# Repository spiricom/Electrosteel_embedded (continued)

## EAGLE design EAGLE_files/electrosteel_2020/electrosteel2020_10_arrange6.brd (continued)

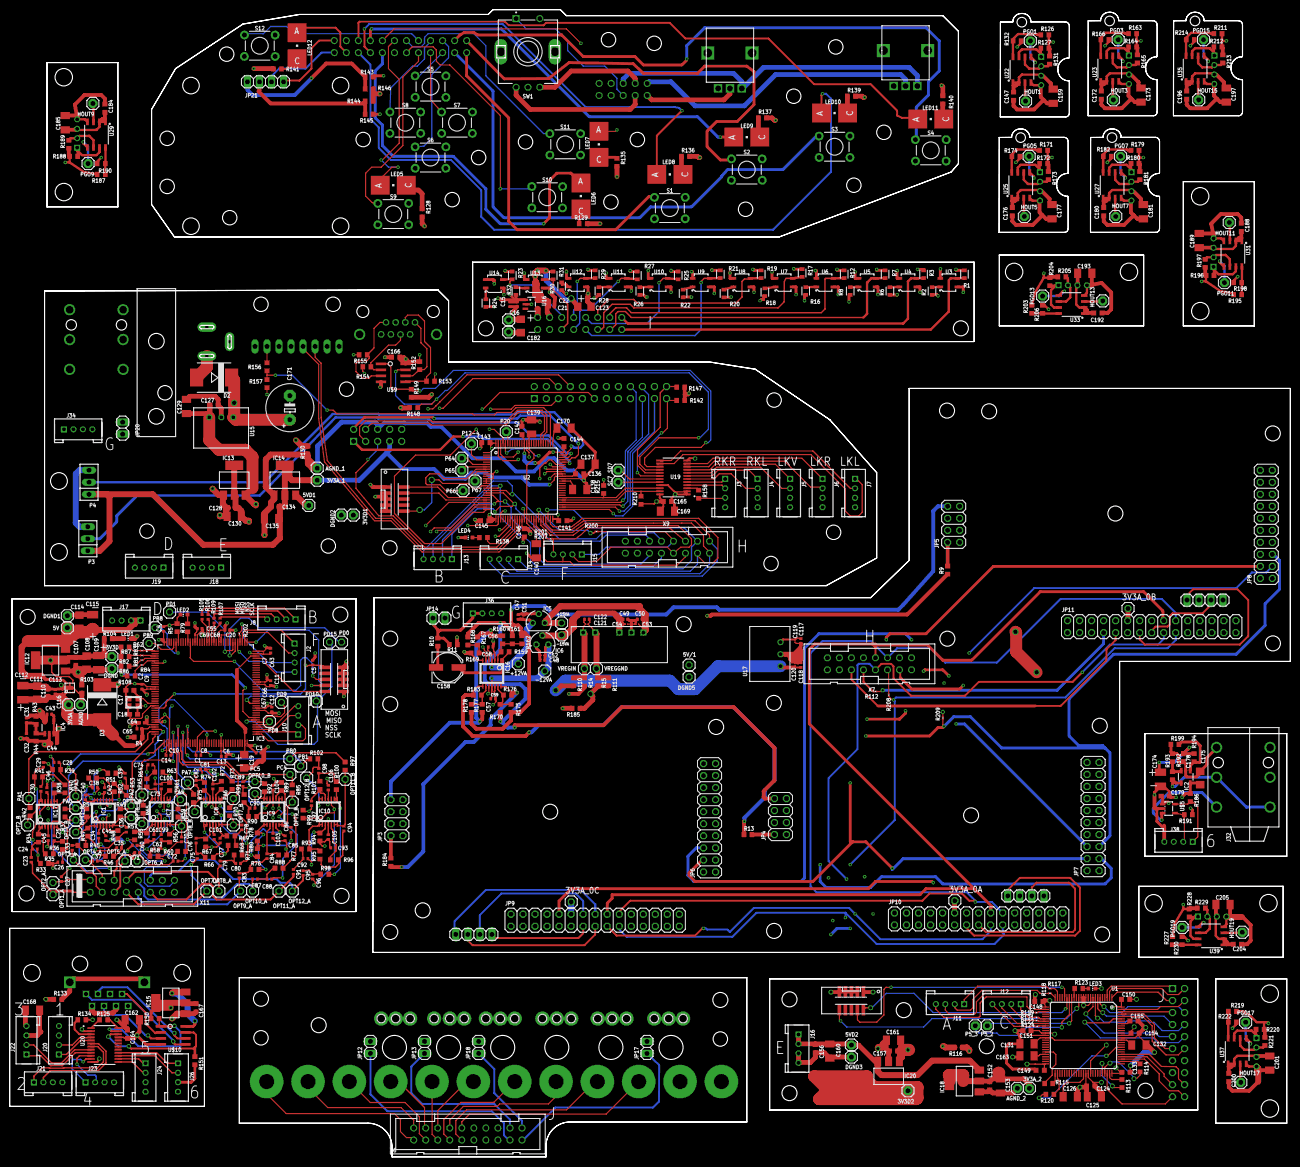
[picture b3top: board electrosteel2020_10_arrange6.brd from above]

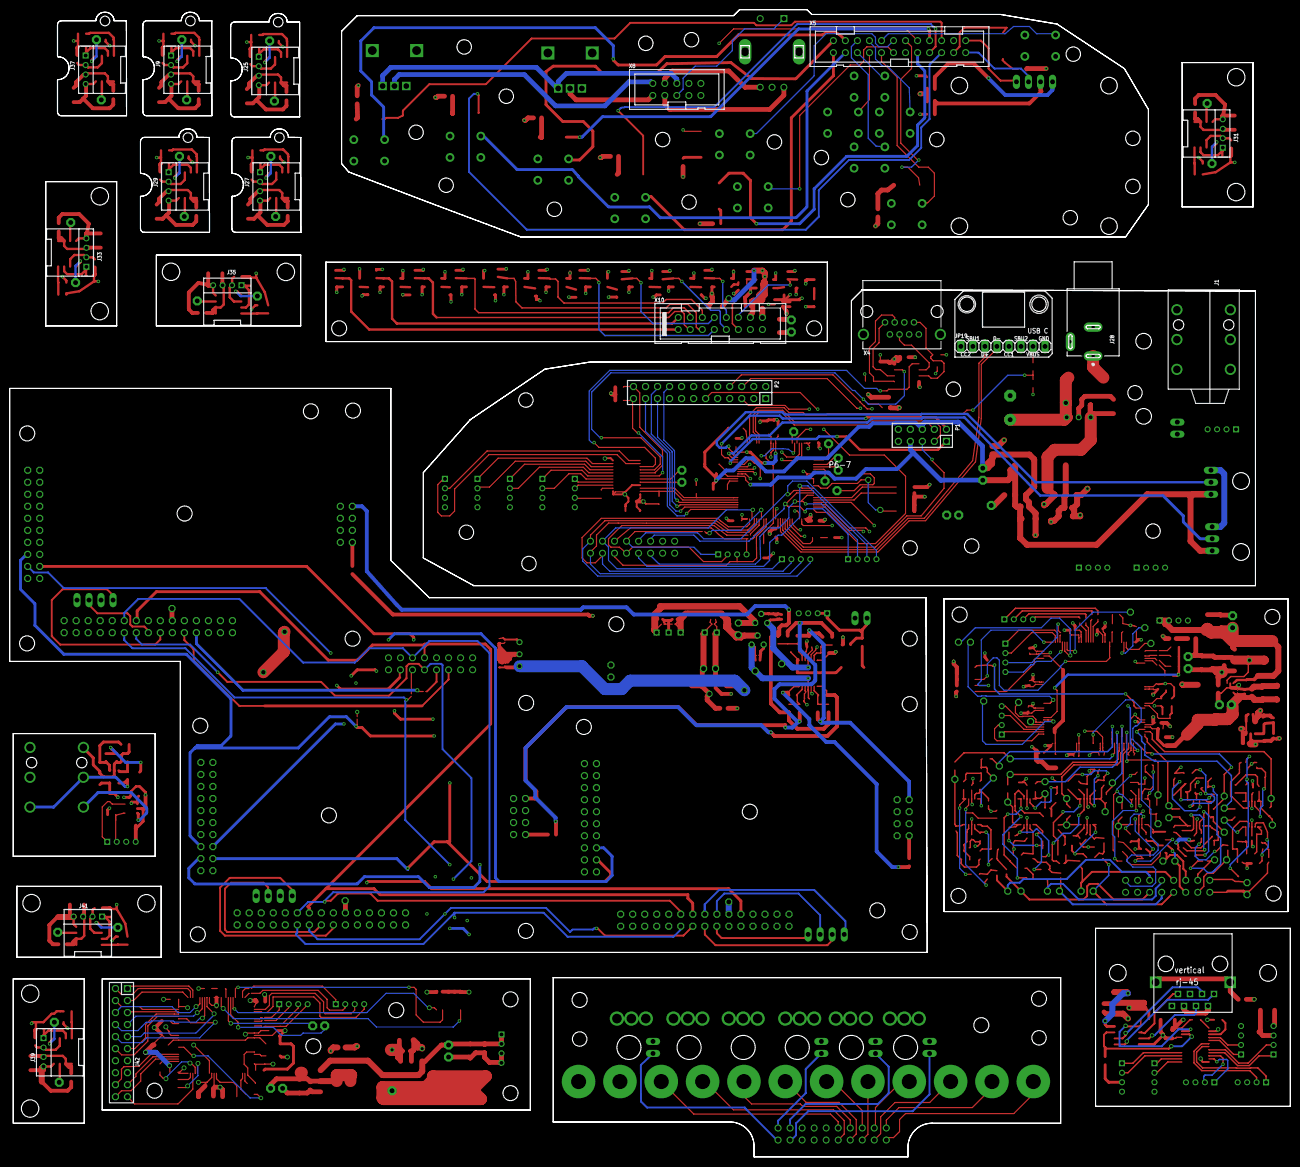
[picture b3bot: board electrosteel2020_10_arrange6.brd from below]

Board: 4 copper layers, 270.5 x 242.3 mm, 678 parts (21 on the bottom side), 529 nets.

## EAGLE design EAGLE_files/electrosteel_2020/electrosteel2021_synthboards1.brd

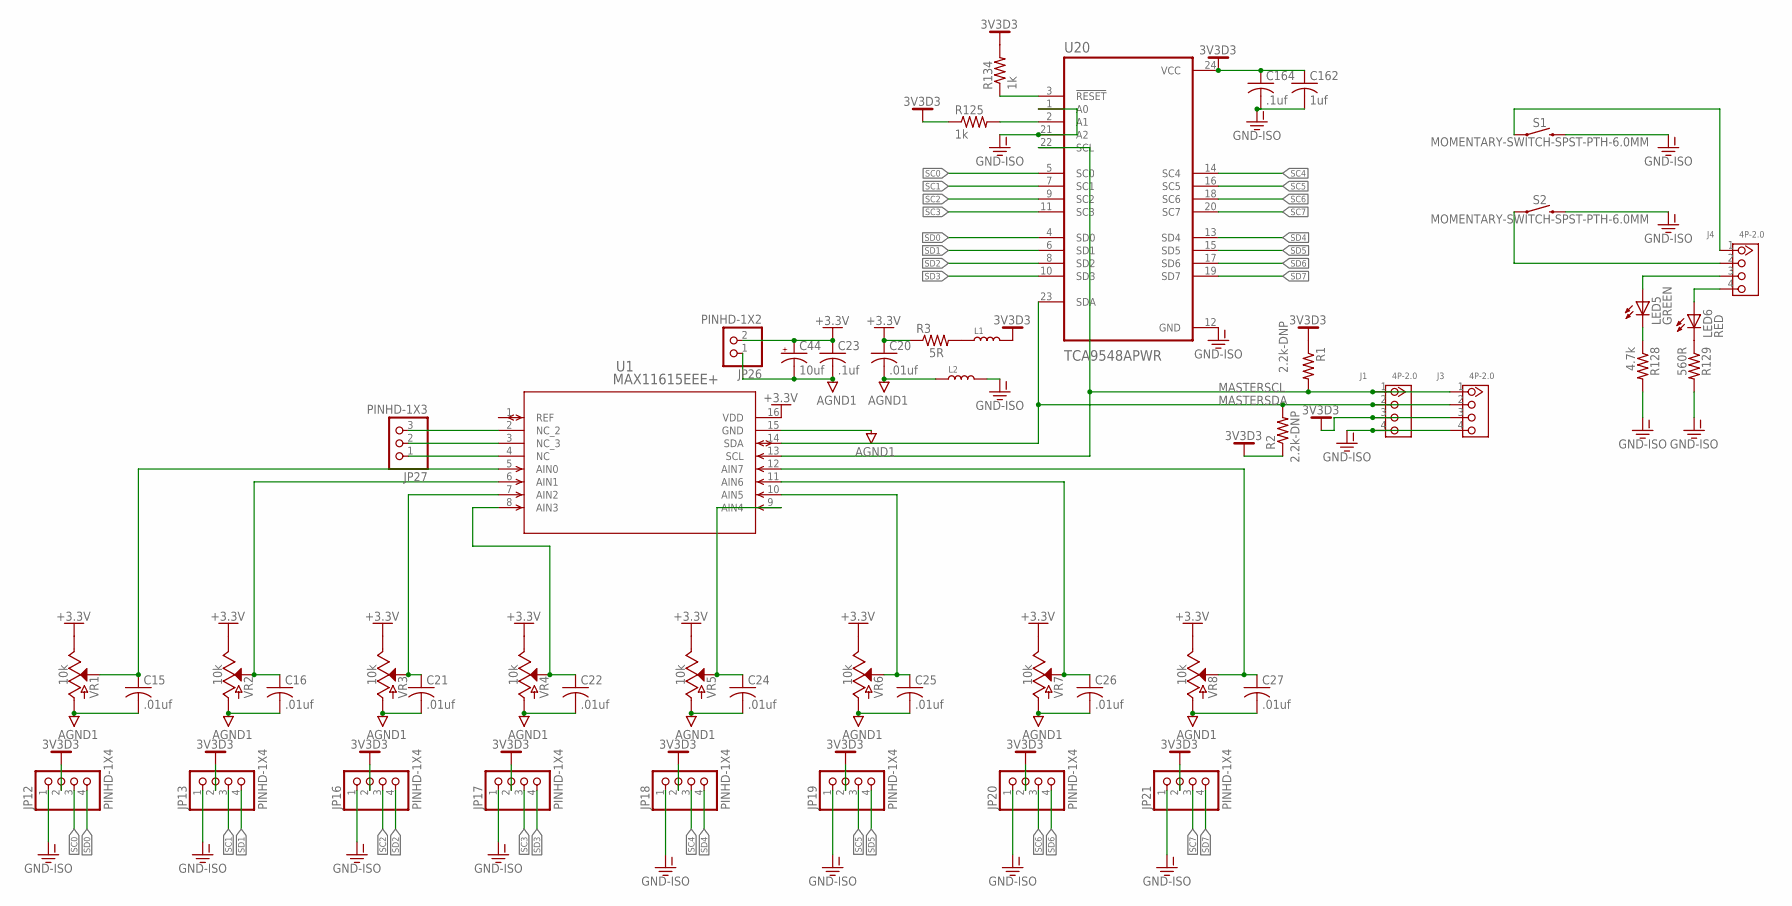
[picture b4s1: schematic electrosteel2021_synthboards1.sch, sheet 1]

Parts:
C15, C16, C20, C21, C22, C24, C25, C26, C27: .01uf; C0603; PARTNO CC0603KRX7R8BB103
C23, C164: .1uf; C0603; PARTNO CC0603KRX7R8BB104
C44: 10uf; SMC_B; PARTNO TAJB106K025RNJ
C162: 1uf; C1206K; PARTNO C3216X7R1E105K085AA
J1, J3, J4: 4P-2.0; HW4-2.0; PARTNO *DNP
JP12, JP13, JP16, JP17, JP18, JP19, JP20, JP21: PINHD-1X4; 1X04; PARTNO *DNP
JP26: PINHD-1X2; 1X02; PARTNO *DNP
JP27: PINHD-1X3; 1X03; PARTNO *DNP
L1, L2: INDUCTOR/FERRITE-BEAD0603; INDUCTOR_L0603; PARTNO FBMH1608HM470-TV
LED5: GREEN; P-LCC-2; PARTNO HSMM-A101-R00J1
LED6: RED; P-LCC-2; PARTNO HSMZ-A100-R00J1
R1, R2: 2.2k-DNP; R0603; PARTNO *DNP
R3: 5R; R0603; PARTNO RC0603JR-075R1L
R125, R134: 1k; R0603; PARTNO ESR03EZPF1001
R128: 4.7k; R0603; PARTNO CRCW06034K70FKEAHP
R129: 560R; R0603; PARTNO ESR03EZPF5600
S1, S2: MOMENTARY-SWITCH-SPST-PTH-6.0MM; TACTILE_SWITCH_PTH_6.0MM; PARTNO TL1105SPF160Q
U1: MAX11615EEE+; 21-0055H_16_MXM; PARTNO MAX11617EEE+
U20: TCA9548APWR; SOP65P640X120-24N; PARTNO TCA9548APWR
VR1, VR2, VR3, VR4, VR5, VR6, VR7, VR8: 10k; POT-PTH-ALPS; PARTNO *DNP

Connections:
3V3D3: C162.1, C164.1, J1.3, J3.3, JP12.2, JP13.2, JP16.2, JP17.2, JP18.2, JP19.2, JP20.2, JP21.2, L1.2, R1.1, R2.1, R125.1, R134.2, U20.24 (VCC)
+3.3V: C20.1, C23.1, C44.+, JP26.2, R3.1, U1.16 (VDD), VR1.P$1 (E), VR2.P$1 (E), VR3.P$1 (E), VR4.P$1 (E), VR5.P$1 (E), VR6.P$1 (E), VR7.P$1 (E), VR8.P$1 (E)
AGND1: C15.2, C16.2, C20.2, C21.2, C22.2, C23.2, C24.2, C25.2, C26.2, C27.2, C44.-, JP26.1, L2.1, U1.15 (GND), VR1.P$3 (A), VR2.P$3 (A), VR3.P$3 (A), VR4.P$3 (A), VR5.P$3 (A), VR6.P$3 (A), VR7.P$3 (A), VR8.P$3 (A)
GND-ISO: C162.2, C164.2, J1.4, J3.4, JP12.1, JP13.1, JP16.1, JP17.1, JP18.1, JP19.1, JP20.1, JP21.1, L2.2, R128.2, R129.2, S1.3 (2), S2.3 (2), U20.1 (A0), U20.12 (GND), U20.21 (A2)
MASTERSCL: J1.1, J3.1, R1.2, U1.13 (SCL), U20.22 (SCL)
MASTERSDA: J1.2, J3.2, R2.2, U1.14 (SDA), U20.23 (SDA)
unnamed: LED5.C, R128.1
unnamed: JP27.1, U1.4 (NC)
unnamed: C15.1, U1.5 (AIN0), VR1.P$2 (S)
unnamed: C16.1, U1.6 (AIN1), VR2.P$2 (S)
unnamed: C21.1, U1.7 (AIN2), VR3.P$2 (S)
unnamed: C22.1, U1.8 (AIN3), VR4.P$2 (S)
unnamed: J4.2, S2.1
unnamed: C24.1, U1.9 (AIN4), VR5.P$2 (S)
unnamed: C25.1, U1.10 (AIN5), VR6.P$2 (S)
unnamed: J4.3, LED5.A
unnamed: C26.1, U1.11 (AIN6), VR7.P$2 (S)
unnamed: C27.1, U1.12 (AIN7), VR8.P$2 (S)
unnamed: J4.4, LED6.A
unnamed: JP27.2, U1.3 (NC_3)
unnamed: R125.2, U20.2 (A1)
unnamed: JP27.3, U1.2 (NC_2)
unnamed: L1.1, R3.2
unnamed: J4.1, S1.1
unnamed: R134.1, U20.3 (!RESET)
unnamed: LED6.C, R129.1
SC0: JP12.3, U20.5 (SC0)
SC1: JP13.3, U20.7 (SC1)
SC2: JP16.3, U20.9 (SC2)
SC3: JP17.3, U20.11 (SC3)
SC4: JP18.3, U20.14 (SC4)
SC5: JP19.3, U20.16 (SC5)
SC6: JP20.3, U20.18 (SC6)
SC7: JP21.3, U20.20 (SC7)
SD0: JP12.4, U20.4 (SD0)
SD1: JP13.4, U20.6 (SD1)
SD2: JP16.4, U20.8 (SD2)
SD3: JP17.4, U20.10 (SD3)
SD4: JP18.4, U20.13 (SD4)
SD5: JP19.4, U20.15 (SD5)
SD6: JP20.4, U20.17 (SD6)
SD7: JP21.4, U20.19 (SD7)

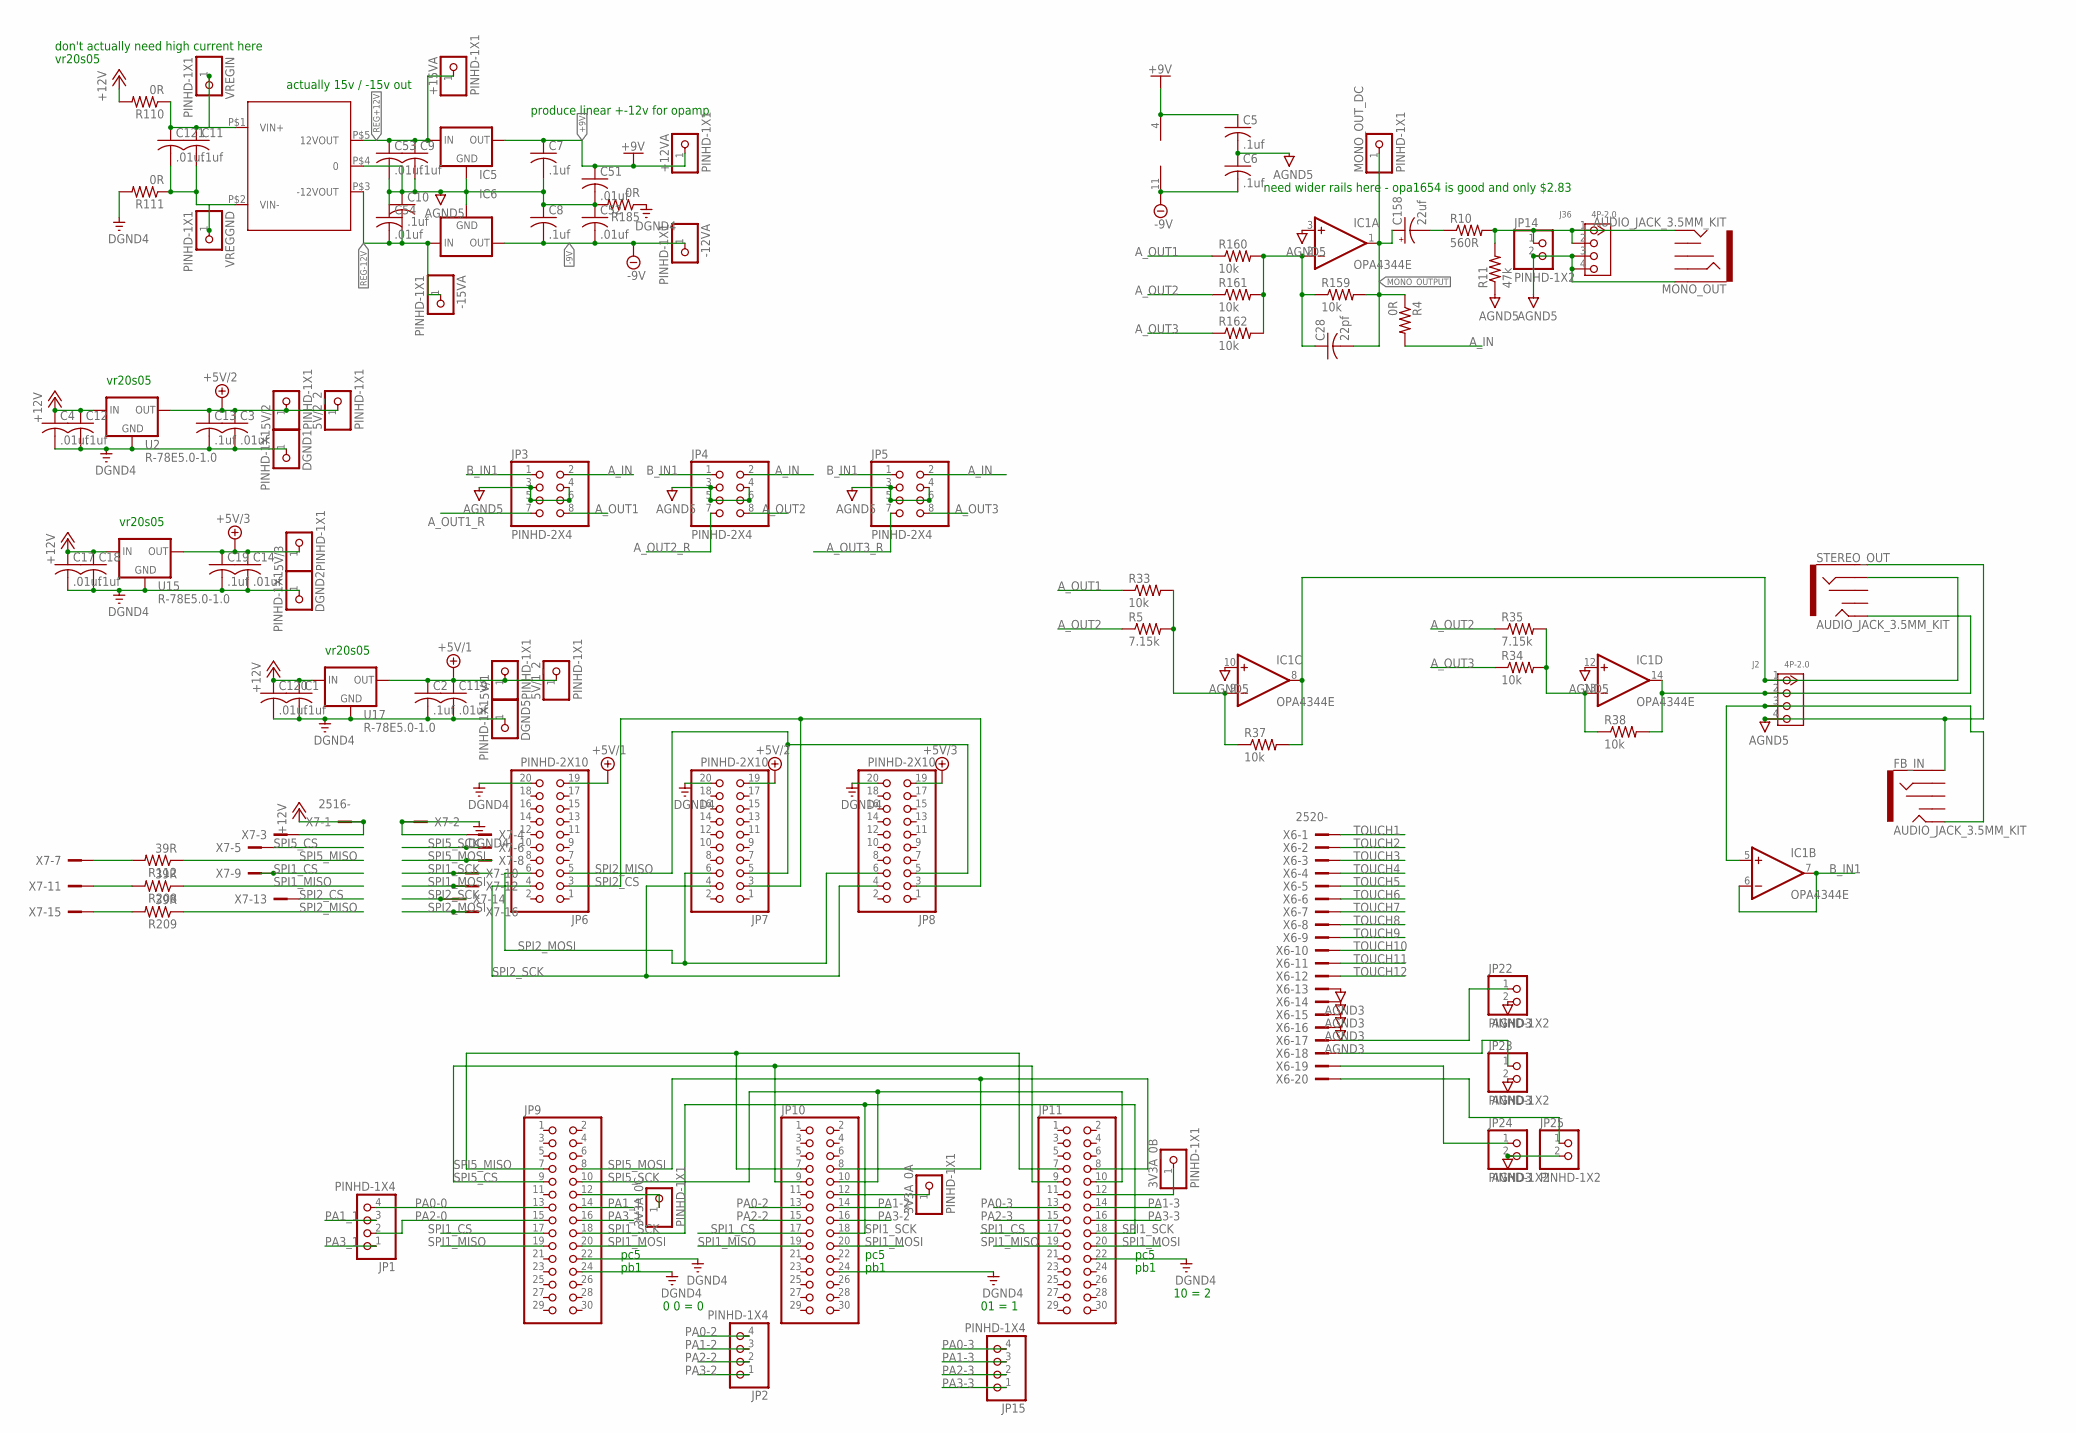
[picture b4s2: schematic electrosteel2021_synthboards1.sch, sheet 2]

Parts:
3V3A_0A, 3V3A_0B, 3V3A_0C, 5V/1, 5V/1_2, 5V/2, 5V/2_2, 5V/3: PINHD-1X1; 1X01; PARTNO *DNP
+12VA, +15VA: PINHD-1X1; 1X01; PARTNO *DNP
-12VA, -15VA: PINHD-1X1; 1X01; PARTNO *DNP
C1, C2, C5, C6, C7, C8, C9, C10, C11, C12, C13, C18, C19: .1uf; C0603; PARTNO CC0603KRX7R8BB104
C3, C4, C14, C17, C51, C52, C53, C54, C119, C120, C121: .01uf; C0603; PARTNO CC0603KRX7R8BB103
C28: 22pf; C0603; PARTNO CC0603JRNPO9BN220
C158: 22uf; PANASONIC_D; PARTNO EEE-1CA220NP
DGND1, DGND2, DGND5: PINHD-1X1; 1X01; PARTNO *DNP
FB_IN: AUDIO_JACK_3.5MM_KIT; AUDIO-JACK-KIT; PARTNO PRT-08032
IC1: OPA4344E; TSSOP14; PARTNO OPA1664AIPWR
IC5: 78LXX; PARTNO LM78L12ACZ/LFT7
IC6: 79LXX; PARTNO L79L12ACZ-TR
J2, J36: 4P-2.0; HW4-2.0; PARTNO *DNP
JP1, JP2, JP15: PINHD-1X4; 1X04; PARTNO *DNP
JP3, JP4, JP5: PINHD-2X4; 2X04; PARTNO 77313-101-08LF
JP6, JP7, JP8: PINHD-2X10; 2X10; PARTNO 77313-101-20LF
JP9, JP10, JP11: PINHD-2X15; 2X15; PARTNO 77313-101-30LF
JP14, JP22, JP23, JP24, JP25: PINHD-1X2; 1X02; PARTNO *DNP
MONO_OUT: AUDIO_JACK_3.5MM_KIT; AUDIO-JACK-KIT; PARTNO PRT-08032
MONO_OUT_DC: PINHD-1X1; 1X01; PARTNO *DNP
R4, R110, R111, R185: 0R; R0603; PARTNO RCS06030000Z0EA
R5, R35: 7.15k; R0603; PARTNO ERJ-3EKF7151V
R10: 560R; R0603; PARTNO ESR03EZPF5600
R11: 47k; R0603; PARTNO ESR03EZPJ473
R33, R34, R37, R38, R159, R160, R161, R162: 10k; R0603; PARTNO ESR03EZPF1002
R112, R208, R209: 39R; R0603; PARTNO RC0603JR-0739RL
STEREO_OUT: AUDIO_JACK_3.5MM_KIT; AUDIO-JACK-KIT; PARTNO PRT-08032
U2, U15, U17: R-78E5.0-1.0; DC-DC_CONVERTER_78XX; PARTNO R-78E5.0-1.0
U$3: CMR0512S3C; PARTNO DPU01M-15
VREGGND: PINHD-1X1; 1X01; PARTNO *DNP
VREGIN: PINHD-1X1; 1X01; PARTNO *DNP
X6: 2520-; PAK100/2500-20; PARTNO N2520-6003-UG
X7: 2516-; PAK100/2500-16; PARTNO D2516-6002-AR

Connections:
+5V/1: 5V/1.1, 5V/1_2.1, C2.1, C119.1, JP6.19, U17.VOUT (OUT)
+5V/2: 5V/2.1, 5V/2_2.1, C3.1, C13.1, JP7.19, U2.VOUT (OUT)
+5V/3: 5V/3.1, C14.1, C19.1, JP8.19, U15.VOUT (OUT)
+9V: +12VA.1, C5.1, C7.1, C51.1, IC1.4 (V+), IC5.OUT
+12V: C1.1, C4.1, C12.1, C17.1, C18.1, C120.1, R110.2, U2.VIN (IN), U15.VIN (IN), U17.VIN (IN), X7.1, X7.3
-9V: -12VA.1, C6.2, C8.2, C52.2, IC1.11 (V-), IC6.OUT
AGND3: JP22.2, JP23.2, JP24.2, JP25.2, X6.13, X6.14, X6.15, X6.16
AGND5: C5.2, C6.1, C7.2, C8.1, C9.2, C10.1, C51.2, C52.1, C53.2, C54.1, FB_IN.SLEEVE, IC1.3 (+IN), IC1.10 (+IN), IC1.12 (+IN), IC5.GND, IC6.GND, J2.4, J36.3, J36.4, JP3.3, JP3.4, JP3.5, JP3.6, JP4.3, JP4.4, JP4.5, JP4.6, JP5.3, JP5.4, JP5.5, JP5.6, JP14.2, MONO_OUT.SLEEVE, R11.1, R185.2, STEREO_OUT.SLEEVE, U$3.P$4 (0)
A_IN: JP3.2, JP4.2, JP5.2, R4.2
A_OUT1: JP3.8, R33.1, R160.1
A_OUT1_R: JP3.7
A_OUT2: JP4.8, R5.1, R35.1, R161.1
A_OUT2_R: JP4.7
A_OUT3: JP5.8, R34.1, R162.1
A_OUT3_R: JP5.7
B_IN1: IC1.6 (-IN), IC1.7 (OUT), JP3.1, JP4.1, JP5.1
DGND4: C1.2, C2.2, C3.2, C4.2, C12.2, C13.2, C14.2, C17.2, C18.2, C19.2, C119.2, C120.2, DGND1.1, DGND2.1, DGND5.1, JP6.20, JP7.20, JP8.20, JP9.22, JP9.24, JP10.24, JP11.22, R111.2, R185.1, U2.GND, U15.GND, U17.GND, X7.2, X7.4
MONO_OUTPUT: C28.2, C158.+, IC1.1 (OUT), MONO_OUT_DC.1, R4.1, R159.2
unnamed: IC1.9 (-IN), R5.2, R33.2, R37.1
unnamed: IC1.13 (-IN), R34.2, R35.2, R38.1
unnamed: IC1.14 (OUT), J2.2, R38.2, STEREO_OUT.TIP
unnamed: IC1.8 (OUT), J2.1, R37.2, STEREO_OUT.RING
unnamed: JP24.1, X6.19
unnamed: FB_IN.TIP, IC1.5 (+IN), J2.3
unnamed: JP25.1, X6.20
unnamed: JP23.1, X6.18
unnamed: JP22.1, X6.17
unnamed: C28.1, IC1.2 (-IN), R159.1, R160.2, R161.2, R162.2
unnamed: C11.2, C121.2, R111.1, U$3.P$2 (VIN-), VREGGND.1
unnamed: C11.1, C121.1, R110.1, U$3.P$1 (VIN+), VREGIN.1
unnamed: C158.-, R10.1
unnamed: J36.1, J36.2, JP14.1, MONO_OUT.TIP, R10.2, R11.2
unnamed: R209.2, X7.15
unnamed: R208.2, X7.11
unnamed: R112.2, X7.7
unnamed: 3V3A_0C.1, JP9.12
unnamed: 3V3A_0A.1, JP10.12
unnamed: 3V3A_0B.1, JP11.12
PA0-0: JP1.4, JP9.13
PA0-2: JP2.4, JP10.13
PA0-3: JP11.13, JP15.4
PA1-2: JP2.3, JP10.14
PA1-3: JP11.14, JP15.3
PA1_1: JP1.3, JP9.14
PA2-0: JP1.2, JP9.15
PA2-2: JP2.2, JP10.15
PA2-3: JP11.15, JP15.2
PA3-2: JP2.1, JP10.16
PA3-3: JP11.16, JP15.1
PA3_1: JP1.1, JP9.16
REG+12V: +15VA.1, C9.1, C53.1, IC5.IN, U$3.P$5 (12VOUT)
REG-12V: -15VA.1, C10.2, C54.2, IC6.IN, U$3.P$3 (-12VOUT)
SPI1_CS: JP9.17, JP10.17, JP11.17, X7.9
SPI1_MISO: JP9.19, JP10.19, JP11.19, R208.1
SPI1_MOSI: JP9.20, JP10.20, JP11.20, X7.12
SPI1_SCK: JP9.18, JP10.18, JP11.18, X7.10
SPI2_CS: JP6.3, JP7.3, JP8.3, X7.13
SPI2_MISO: JP6.5, JP7.5, JP8.5, R209.1
SPI2_MOSI: JP6.6, JP7.6, JP8.6, X7.16
SPI2_SCK: JP6.4, JP7.4, JP8.4, X7.14
SPI5_CS: JP9.9, JP10.9, JP11.9, X7.5
SPI5_MISO: JP9.7, JP10.7, JP11.7, R112.1
SPI5_MOSI: JP9.8, JP10.8, JP11.8, X7.8
SPI5_SCK: JP9.10, JP10.10, JP11.10, X7.6
TOUCH1: X6.1
TOUCH2: X6.2
TOUCH3: X6.3
TOUCH4: X6.4
TOUCH5: X6.5
TOUCH6: X6.6
TOUCH7: X6.7
TOUCH8: X6.8
TOUCH9: X6.9
TOUCH10: X6.10
TOUCH11: X6.11
TOUCH12: X6.12

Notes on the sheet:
produce linear +-12v for opamp
vr20s05
0 0 = 0
01 = 1
10 = 2
don't actually need high current here
pc5
pb1
need wider rails here - opa1654 is good and only $2.83
actually 15v / -15v out

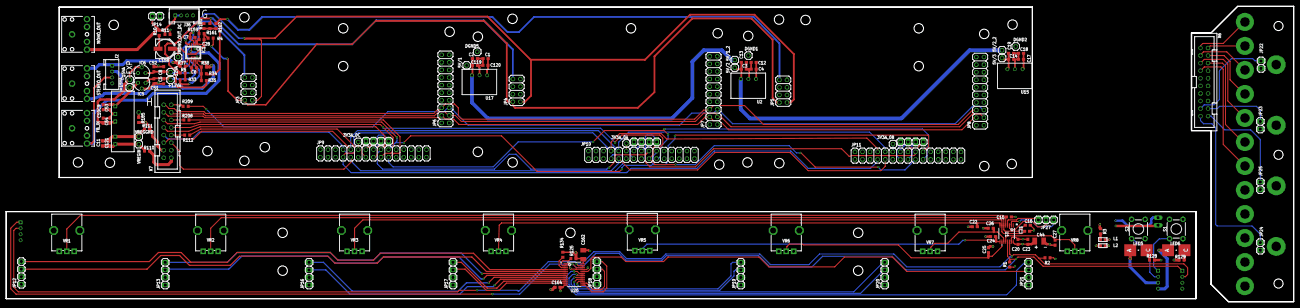
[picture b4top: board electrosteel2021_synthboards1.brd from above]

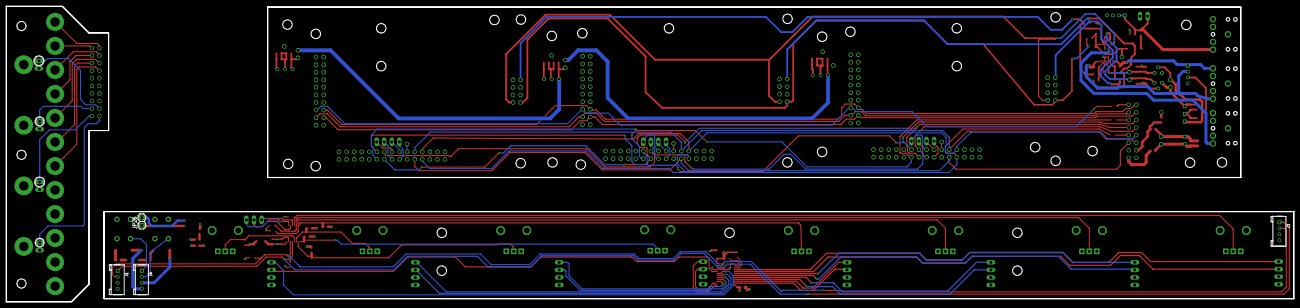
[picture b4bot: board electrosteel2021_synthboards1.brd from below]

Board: 4 copper layers, 431.8 x 99.1 mm, 143 parts (4 on the bottom side), 103 nets.

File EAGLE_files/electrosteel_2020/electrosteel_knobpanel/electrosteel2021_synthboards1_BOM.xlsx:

electrosteel2021_synthboards1_GenericPartsOrder
Mfg Part Num | Mfg Name | VID | Vendor Part Num | Description | Pkg Code | Qty-1 | Qty-5 | Qty-25 | Part References | Value
77313-101-30LF | Amphenol | DK | 609-77313-101-30LF-ND | CONN HEADER VERT 30POS 2.54MM | TH | 3 | 15 | 75 | JP9, JP10, JP11
FBMH1608HM470-TV | Taiyo Yuden | DK | 587-3824-2-ND | FERRITE BEAD 47 OHM 0603 1LN | 603 | 2 | 10 | 50 | L1, L2
L79L12ACZ-TR | ST | DK | 497-7302-2-ND | IC REG LINEAR -12V 100MA TO92-3 | TO92-3 | 1 | 5 | 25 | IC6
LM78L12ACZ/LFT7 | TI | DK | 296-LM78L12ACZ/LFT7TR-ND | IC REG LINEAR 12V 100MA TO92-3 | TO92-3 | 1 | 5 | 25 | IC5
CC0603KRX7R8BB104 | Yageo | DK | 311-1341-1-ND | CAP CER 0.1UF 25V 10% X7R 0603 | 603 | 15 | 75 | 375 | C1, C2, C5, C6, C7, C8, C9, C10, C11, C12, C13, C18, C19, C23, C164 | .1uf
CC0603KRX7R8BB103 | Yageo | DK | 311-1360-1-ND | CAP CER 10000PF 25V 10% X7R 0603 | 603 | 20 | 100 | 500 | C3, C4, C14, C15, C16, C17, C20, C21, C22, C24, C25, C26, C27, C51, C52, C53, C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 | .01uf
RCS06030000Z0EA | Vishay | DK | 541-2779-1-ND | RES SMD 0 OHM JUMPER 1/4W 0603 | 603 | 4 | 20 | 100 | R4, R110, R111, R185 | 0R
ESR03EZPF1001 | Rohm | DK | RHM1.00KADCT-ND | RES 1K OHM 1/4W 1% 0603 SMD | 603 | 2 | 10 | 50 | R125, R134 | 1k
C3216X7R1E105K085AA | TDK | DK | 445-1592-1-ND | CAP CER 1UF 25V 10% X7R 1206 | 1206 | 1 | 5 | 25 | C162 | 1uf
*DNP | DO NOT PLACE | (N/A) | DO NOT PLACE | DO NOT PLACE | * | 2 | 10 | 50 | R1, R2 | 2.2k-DNP
CRCW06034K70FKEAHP | Vishay Dale | DK | 541-4.70KSCT-ND | RES 4.70K OHM .25W 1% 0603 SMD | 603 | 1 | 5 | 25 | R128 | 4.7k
*DNP | DO NOT PLACE | (N/A) | DO NOT PLACE | DO NOT PLACE | * | 5 | 25 | 125 | J1, J2, J3, J4, J36 | 4P-2.0
RC0603JR-075R1L | Yageo | DK | 311-5.1GRCT-ND | RES SMD 5.1 OHM 5% 1/10W 0603 | 603 | 1 | 5 | 25 | R3 | 5R
ERJ-3EKF7151V | Panasonic | DK | P7.15KHTR-ND | RES SMD 7.15K OHM 1% 1/10W 0603 | 603 | 2 | 10 | 50 | R5, R35 | 7.15k
*DNP | DO NOT PLACE | (N/A) | DO NOT PLACE | DO NOT PLACE | * | 8 | 40 | 200 | VR1, VR2, VR3, VR4, VR5, VR6, VR7, VR8 | 10k
ESR03EZPF1002 | Rohm | DK | RHM10KADCT-ND | RES 10K OHM 1/4W 1% 0603 SMD | 603 | 8 | 40 | 200 | R33, R34, R37, R38, R159, R160, R161, R162 | 10k
TAJB106K025RNJ | AVX | DK | 478-5257-1-ND | 10µF ±10% Molded Tantalum Capacitors 25V | 1210 | 1 | 5 | 25 | C44 | 10uf
CC0603JRNPO9BN220 | Yageo | DK | 311-1062-1-ND | CAP CER 22PF 50V 5% NPO 0603 | 603 | 1 | 5 | 25 | C28 | 22pf
EEE-1CA220NP | Panasonic | DK | PCE4306CT-ND | CAP ALUM 22UF 20% 16V SMD Bipolar | PANASONIC_C | 1 | 5 | 25 | C158 | 22uf
RC0603JR-0739RL | Yageo | DK | 311-39GRCT-ND | RES SMD 39 OHM 5% 1/10W 0603 | 603 | 3 | 15 | 75 | R112, R208, R209 | 39R
ESR03EZPJ473 | Rohm | DK | RHM47KDCT-ND | RES 47K OHM 1/4W 5% 0603 SMD | 603 | 1 | 5 | 25 | R11 | 47k
ESR03EZPF5600 | Rohm | DK | RHM560ADCT-ND | RES 560 OHM 1/4W 1% 0603 SMD | 603 | 2 | 10 | 50 | R10, R129 | 560R
D2516-6002-AR | 3M | DK | MHC16E-ND | CONN HEADER VERT 16POS 2.54MM | TH | 1 | 5 | 25 | X7 | -2516
N2520-6003-UG | 3M | DK | N2520-6003-UG-ND | CONN HEADER VERT 20POS 2.54MM | TH | 1 | 5 | 25 | X6 | -2520
PRT-08032 | Generic | Sparkfun | PRT-08032 | Audio Jack 3.5mm stereo | TH | 3 | 15 | 75 | FB_IN, MONO_OUT, STEREO_OUT | AUDIO_JACK_3.5MM_KIT
DPU01M-15 | MeanWell | DK | 1866-1412-ND | DC DC CONVERTER +/-15V 1W | 7-SIP | 1 | 5 | 25 | U$3 | CMR0512S3C
HSMM-A101-R00J1 | Broadcom | DK | 516-2124-1-ND | LED GREEN CLEAR 2PLCC SMD | 2PLCC | 1 | 5 | 25 | LED5 | GREEN
MAX11617EEE+ | Maxim | MO | 700-MAX11617EEE | Analog to Digital Converters - ADC 2.7V to 3.6V and 4.5V to 5.5V Low-Power 4-/8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 | QSOP-16 | 1 | 5 | 25 | U1 | MAX11615EEE+
TL1105SPF160Q | E-Switch | DK | EG1861-ND | SWITCH TACTILE SPST-NO 0.05A 12V | TH | 2 | 10 | 50 | S1, S2 | MOMENTARY-SWITCH-SPST-PTH-6.0MM
OPA1664AIPWR | TI | DK | 296-40431-2-ND | IC AUDIO 4 CIRCUIT 14TSSOP | 14TSSOP | 1 | 5 | 25 | IC1 | OPA4344E
*DNP | DO NOT PLACE | (N/A) | DO NOT PLACE | DO NOT PLACE | * | 18 | 90 | 450 | +12VA, +15VA, -12VA, -15VA, 3V3A_0A, 3V3A_0B, 3V3A_0C, 5V/1, 5V/1_2, 5V/2, 5V/2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 | PINHD-1X1
*DNP | DO NOT PLACE | (N/A) | DO NOT PLACE | DO NOT PLACE | * | 6 | 30 | 150 | JP14, JP22, JP23, JP24, JP25, JP26 | PINHD-1X2
*DNP | DO NOT PLACE | (N/A) | DO NOT PLACE | DO NOT PLACE | * | 1 | 5 | 25 | JP27 | PINHD-1X3
*DNP | DO NOT PLACE | (N/A) | DO NOT PLACE | DO NOT PLACE | * | 11 | 55 | 275 | JP1, JP2, JP12, JP13, JP15, JP16, JP17, JP18, JP19, JP20, JP21 | PINHD-1X4
77313-101-08LF | Amphenol | DK | 609-5693-ND | CONN HEADER VERT 8POS 2.54MM | TH | 3 | 15 | 75 | JP3, JP4, JP5 | PINHD-2X4
77313-101-20LF | Amphenol | DK | 609-5697-ND | CONN HEADER VERT 20POS 2.54MM | TH | 3 | 15 | 75 | JP6, JP7, JP8 | PINHD-2X10
R-78E5.0-1.0 | Recom | DK | 945-2201-ND | 5V Switching Regulator | TH | 3 | 15 | 75 | U2, U15, U17 | R-78E5.0-1.0
HSMZ-A100-R00J1 | Broadcom | DK | 516-1459-1-ND | LED RED CLEAR 2PLCC SMD | 2PLCC | 1 | 5 | 25 | LED6 | RED
TCA9548APWR | Texas Instruments | DK | 296-34905-1-ND | IC I2C SW 8CH W/RESET 24TSSOP | 24TSSOP | 1 | 5 | 25 | U20 | TCA9548APWR

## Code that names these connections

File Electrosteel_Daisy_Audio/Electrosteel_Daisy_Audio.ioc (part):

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Mcu.Name=STM32H750IBKx
Mcu.Package=UFBGA176+25
Mcu.UserName=STM32H750IBKx
PA0.Signal=GPIO_Output
PA1.Signal=GPIO_Input
PA13\ (JTMS/SWDIO).Mode=Trace_Asynchronous_SW
PA13\ (JTMS/SWDIO).Signal=DEBUG_JTMS-SWDIO
PA14\ (JTCK/SWCLK).Mode=Trace_Asynchronous_SW
PA14\ (JTCK/SWCLK).Signal=DEBUG_JTCK-SWCLK
PA2.GPIOParameters=GPIO_PuPd
PA2.GPIO_PuPd=GPIO_PULLUP
PA2.Signal=GPIO_Input
PA3.Signal=S_TIM2_CH4
PA4.GPIOParameters=GPIO_Speed
PA4.GPIO_Speed=GPIO_SPEED_FREQ_HIGH
PA4.Mode=NSS_Signal_Hard_Input
PA4.Signal=SPI6_NSS
PA5.GPIOParameters=GPIO_Speed
PA5.GPIO_Speed=GPIO_SPEED_FREQ_HIGH
PA5.Mode=Full_Duplex_Slave
PA5.Signal=SPI6_SCK
PA6.GPIOParameters=GPIO_Speed
PA6.GPIO_Speed=GPIO_SPEED_FREQ_HIGH
PA6.Mode=Full_Duplex_Slave
PA6.Signal=SPI6_MISO
PA7.GPIOParameters=GPIO_Speed
PA7.GPIO_Speed=GPIO_SPEED_FREQ_HIGH
PA7.Mode=Full_Duplex_Slave
PA7.Signal=SPI6_MOSI
PB1.Signal=S_TIM3_CH4
PB11.GPIOParameters=GPIO_Speed
PB11.GPIO_Speed=GPIO_SPEED_FREQ_VERY_HIGH
PB11.Mode=I2C
PB11.Signal=I2C2_SDA
PB12.GPIOParameters=GPIO_ModeDefaultEXTI
PB12.GPIO_ModeDefaultEXTI=GPIO_MODE_IT_RISING
PB12.Signal=GPXTI12
PB14.GPIOParameters=GPIO_PuPd
PB14.GPIO_PuPd=GPIO_PULLUP
PB14.Signal=GPIO_Input
PB15.GPIOParameters=GPIO_PuPd
PB15.GPIO_PuPd=GPIO_PULLUP
PB15.Signal=GPIO_Input
PB3\ (JTDO/TRACESWO).Mode=Trace_Asynchronous_SW
PB3\ (JTDO/TRACESWO).Signal=DEBUG_JTDO-SWO
PB4\ (NJTRST).GPIOParameters=GPIO_Speed
PB4\ (NJTRST).GPIO_Speed=GPIO_SPEED_FREQ_VERY_HIGH
PB4\ (NJTRST).Mode=Full_Duplex_Slave
PB4\ (NJTRST).Signal=SPI1_MISO
PB5.GPIOParameters=GPIO_Speed
PB5.GPIO_Speed=GPIO_SPEED_FREQ_VERY_HIGH
PB5.Mode=Full_Duplex_Slave
PB5.Signal=SPI1_MOSI
PB6.GPIOParameters=GPIO_PuPd,GPIO_ModeDefaultEXTI
PB6.GPIO_ModeDefaultEXTI=GPIO_MODE_IT_FALLING
PB6.GPIO_PuPd=GPIO_PULLUP
PB6.Signal=GPXTI6
PB7.Signal=GPIO_Output
PB8.GPIOParameters=GPIO_Speed
PB8.GPIO_Speed=GPIO_SPEED_FREQ_HIGH
PB8.Mode=I2C
PB8.Signal=I2C1_SCL
PB9.GPIOParameters=GPIO_Speed
PB9.GPIO_Speed=GPIO_SPEED_FREQ_HIGH
PB9.Mode=I2C
PB9.Signal=I2C1_SDA
PC0.Signal=GPIO_Output
PC1.Signal=GPIO_Output
PC10.GPIOParameters=GPIO_PuPd,GPIO_Speed_High_Default
PC10.GPIO_PuPd=GPIO_NOPULL
PC10.GPIO_Speed_High_Default=GPIO_SPEED_FREQ_HIGH
PC10.Mode=SD_4_bits_Wide_bus
PC10.Signal=SDMMC1_D2
PC11.GPIOParameters=GPIO_PuPd,GPIO_Speed_High_Default
PC11.GPIO_PuPd=GPIO_NOPULL
PC11.GPIO_Speed_High_Default=GPIO_SPEED_FREQ_HIGH
PC11.Mode=SD_4_bits_Wide_bus
PC11.Signal=SDMMC1_D3
PC12.GPIOParameters=GPIO_PuPd,GPIO_Speed_High_Default
PC12.GPIO_PuPd=GPIO_NOPULL
PC12.GPIO_Speed_High_Default=GPIO_SPEED_FREQ_HIGH
PC12.Mode=SD_4_bits_Wide_bus
PC12.Signal=SDMMC1_CK
PC4.Signal=GPIO_Output
PC7.Signal=GPIO_Output
PC8.GPIOParameters=GPIO_PuPd,GPIO_Speed_High_Default
PC8.GPIO_PuPd=GPIO_NOPULL
PC8.GPIO_Speed_High_Default=GPIO_SPEED_FREQ_HIGH
PC8.Mode=SD_4_bits_Wide_bus
PC8.Signal=SDMMC1_D0
PC9.GPIOParameters=GPIO_PuPd,GPIO_Speed_High_Default
PC9.GPIO_PuPd=GPIO_NOPULL
PC9.GPIO_Speed_High_Default=GPIO_SPEED_FREQ_HIGH
PC9.Mode=SD_4_bits_Wide_bus
PC9.Signal=SDMMC1_D1
PD0.Signal=FMC_D2_DA2
PD1.Signal=FMC_D3_DA3
PD10.Signal=FMC_D15_DA15
PD11.Signal=GPIO_Output
PD14.Signal=FMC_D0_DA0
PD15.Signal=FMC_D1_DA1
PD2.GPIOParameters=GPIO_PuPd,GPIO_Speed_High_Default
PD2.GPIO_PuPd=GPIO_NOPULL
PD2.GPIO_Speed_High_Default=GPIO_SPEED_FREQ_HIGH
PD2.Mode=SD_4_bits_Wide_bus
PD2.Signal=SDMMC1_CMD
PD8.Signal=FMC_D13_DA13
PD9.Signal=FMC_D14_DA14
PE0.Signal=FMC_NBL0
PE1.Signal=FMC_NBL1
PE10.Signal=FMC_D7_DA7
PE11.Signal=FMC_D8_DA8
PE12.Signal=FMC_D9_DA9
PE13.Signal=FMC_D10_DA10
PE14.Signal=FMC_D11_DA11
PE15.Signal=FMC_D12_DA12
PE2.GPIOParameters=GPIO_Speed
PE2.GPIO_Speed=GPIO_SPEED_FREQ_HIGH
PE2.Mode=SAI_A_MasterWithClock
PE2.Signal=SAI1_MCLK_A
PE3.GPIOParameters=GPIO_Speed
PE3.GPIO_Speed=GPIO_SPEED_FREQ_HIGH
PE3.Mode=SAI_B_SyncSlave
PE3.Signal=SAI1_SD_B
PE4.GPIOParameters=GPIO_Speed
PE4.GPIO_Speed=GPIO_SPEED_FREQ_HIGH
PE4.Mode=SAI_A_MasterWithClock
PE4.Signal=SAI1_FS_A
PE5.GPIOParameters=GPIO_Speed
PE5.GPIO_Speed=GPIO_SPEED_FREQ_HIGH
PE5.Mode=SAI_A_MasterWithClock
PE5.Signal=SAI1_SCK_A
PE6.GPIOParameters=GPIO_Speed
PE6.GPIO_Speed=GPIO_SPEED_FREQ_HIGH
PE6.Mode=SAI_A_MasterWithClock
PE6.Signal=SAI1_SD_A
PE7.Signal=FMC_D4_DA4
PE8.Signal=FMC_D5_DA5
PE9.Signal=FMC_D6_DA6
PF0.Signal=FMC_A0
PF1.Signal=FMC_A1
PF11.Signal=FMC_SDNRAS
PF12.Signal=FMC_A6
PF13.Signal=FMC_A7
PF14.Signal=FMC_A8
PF15.Signal=FMC_A9
PF2.Signal=FMC_A2
PF3.Signal=FMC_A3
PF4.Signal=FMC_A4
PF5.Signal=FMC_A5
PG0.Signal=FMC_A10
PG1.Signal=FMC_A11
PG10.GPIOParameters=GPIO_Speed
PG10.GPIO_Speed=GPIO_SPEED_FREQ_VERY_HIGH
PG10.Mode=NSS_Signal_Hard_Input
PG10.Signal=SPI1_NSS
PG11.GPIOParameters=GPIO_Speed
PG11.GPIO_Speed=GPIO_SPEED_FREQ_VERY_HIGH
PG11.Mode=Full_Duplex_Slave
PG11.Signal=SPI1_SCK
PG15.Signal=FMC_SDNCAS
PG2.Signal=FMC_A12
PG3.GPIOParameters=GPIO_ModeDefaultEXTI
PG3.GPIO_ModeDefaultEXTI=GPIO_MODE_IT_RISING_FALLING
PG3.Signal=GPXTI3
PG4.Signal=FMC_A14_BA0
PG5.Signal=FMC_A15_BA1
PG8.Signal=FMC_SDCLK
PG9.Signal=GPIO_Input
PH0-OSC_IN\ (PH0).Mode=HSE-External-Oscillator
PH0-OSC_IN\ (PH0).Signal=RCC_OSC_IN
PH1-OSC_OUT\ (PH1).Mode=HSE-External-Oscillator
PH1-OSC_OUT\ (PH1).Signal=RCC_OSC_OUT
PH10.Signal=FMC_D18
PH11.Signal=FMC_D19
PH12.Signal=FMC_D20
PH13.Signal=FMC_D21
PH14.Signal=FMC_D22
PH15.Signal=FMC_D23
PH2.Mode=SdramChipSelect1_1
PH2.Signal=FMC_SDCKE0
PH3.Mode=SdramChipSelect1_1
PH3.Signal=FMC_SDNE0
PH4.GPIOParameters=GPIO_Speed
PH4.GPIO_Speed=GPIO_SPEED_FREQ_VERY_HIGH
PH4.Mode=I2C
PH4.Signal=I2C2_SCL
PH5.Signal=FMC_SDNWE
PH8.Signal=FMC_D16
PH9.Signal=FMC_D17
PI0.Signal=FMC_D24
PI1.Signal=FMC_D25
PI10.Signal=FMC_D31
PI2.Signal=FMC_D26
PI3.Signal=FMC_D27
PI4.Signal=FMC_NBL2
PI5.Signal=FMC_NBL3
PI6.Signal=FMC_D28
PI7.Signal=FMC_D29
PI9.Signal=FMC_D30
RCC.HSE_VALUE=16000000
RCC.SYSCLKFreq_VALUE=480000000
RCC.SYSCLKSource=RCC_SYSCLKSOURCE_PLLCLK
board=custom

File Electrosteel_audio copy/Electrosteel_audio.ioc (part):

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Mcu.Name=STM32H743ZITx
Mcu.Package=LQFP144
Mcu.UserName=STM32H743ZITx
PA13\ (JTMS/SWDIO).Mode=Trace_Asynchronous_SW
PA13\ (JTMS/SWDIO).Signal=DEBUG_JTMS-SWDIO
PA14\ (JTCK/SWCLK).Mode=Trace_Asynchronous_SW
PA14\ (JTCK/SWCLK).Signal=DEBUG_JTCK-SWCLK
PA4.GPIOParameters=GPIO_Speed,GPIO_PuPd
PA4.GPIO_PuPd=GPIO_NOPULL
PA4.GPIO_Speed=GPIO_SPEED_FREQ_VERY_HIGH
PA4.Mode=NSS_Signal_Hard_Input
PA4.Signal=SPI1_NSS
PA5.GPIOParameters=GPIO_Speed
PA5.GPIO_Speed=GPIO_SPEED_FREQ_VERY_HIGH
PA5.Mode=Full_Duplex_Slave
PA5.Signal=SPI1_SCK
PA6.GPIOParameters=GPIO_Speed
PA6.GPIO_Speed=GPIO_SPEED_FREQ_HIGH
PA6.Mode=Full_Duplex_Slave
PA6.Signal=SPI1_MISO
PA7.GPIOParameters=GPIO_Speed
PA7.GPIO_Speed=GPIO_SPEED_FREQ_VERY_HIGH
PA7.Mode=Full_Duplex_Slave
PA7.Signal=SPI1_MOSI
PB1.GPIOParameters=GPIO_PuPd
PB1.GPIO_PuPd=GPIO_PULLUP
PB1.Signal=GPIO_Input
PB10.GPIOParameters=GPIO_Speed,GPIO_PuPd,GPIO_Pu
PB10.GPIO_Pu=GPIO_PULLUP
PB10.GPIO_PuPd=GPIO_NOPULL
PB10.GPIO_Speed=GPIO_SPEED_FREQ_VERY_HIGH
PB10.Mode=I2C
PB10.Signal=I2C2_SCL
PB11.GPIOParameters=GPIO_Speed,GPIO_Pu
PB11.GPIO_Pu=GPIO_PULLUP
PB11.GPIO_Speed=GPIO_SPEED_FREQ_VERY_HIGH
PB11.Mode=I2C
PB11.Signal=I2C2_SDA
PB12.GPIOParameters=GPIO_Speed
PB12.GPIO_Speed=GPIO_SPEED_FREQ_VERY_HIGH
PB12.Mode=NSS_Signal_Hard_Input
PB12.Signal=SPI2_NSS
PB13.GPIOParameters=GPIO_Speed
PB13.GPIO_Speed=GPIO_SPEED_FREQ_VERY_HIGH
PB13.Mode=Full_Duplex_Slave
PB13.Signal=SPI2_SCK
PB14.GPIOParameters=GPIO_Speed
PB14.GPIO_Speed=GPIO_SPEED_FREQ_HIGH
PB14.Mode=Full_Duplex_Slave
PB14.Signal=SPI2_MISO
PB15.GPIOParameters=GPIO_Speed
PB15.GPIO_Speed=GPIO_SPEED_FREQ_VERY_HIGH
PB15.Mode=Full_Duplex_Slave
PB15.Signal=SPI2_MOSI
PB3\ (JTDO/TRACESWO).Mode=Trace_Asynchronous_SW
PB3\ (JTDO/TRACESWO).Signal=DEBUG_JTDO-SWO
PB4\ (NJTRST).Signal=GPIO_Output
PC0.Signal=FMC_SDNWE
PC10.GPIOParameters=GPIO_PuPd,GPIO_Speed_High_Default,GPIO_Mode
PC10.GPIO_Mode=GPIO_MODE_AF_PP
PC10.GPIO_PuPd=GPIO_PULLUP
PC10.GPIO_Speed_High_Default=GPIO_SPEED_FREQ_MEDIUM
PC10.Mode=SD_4_bits_Wide_bus
PC10.Signal=SDMMC1_D2
PC11.GPIOParameters=GPIO_PuPd,GPIO_Speed_High_Default,GPIO_Mode
PC11.GPIO_Mode=GPIO_MODE_AF_PP
PC11.GPIO_PuPd=GPIO_PULLUP
PC11.GPIO_Speed_High_Default=GPIO_SPEED_FREQ_MEDIUM
PC11.Mode=SD_4_bits_Wide_bus
PC11.Signal=SDMMC1_D3
PC12.GPIOParameters=GPIO_PuPd,GPIO_Speed_High_Default
PC12.GPIO_PuPd=GPIO_PULLUP
PC12.GPIO_Speed_High_Default=GPIO_SPEED_FREQ_MEDIUM
PC12.Mode=SD_4_bits_Wide_bus
PC12.Signal=SDMMC1_CK
PC13.Signal=GPIO_Input
PC14-OSC32_IN\ (OSC32_IN).Signal=GPIO_Output
PC3_C.Mode=SdramChipSelect1_1
PC3_C.Signal=FMC_SDCKE0
PC4.Mode=SdramChipSelect1_1
PC4.Signal=FMC_SDNE0
PC5.GPIOParameters=GPIO_PuPd
PC5.GPIO_PuPd=GPIO_PULLUP
PC5.Signal=GPIO_Input
PC8.GPIOParameters=GPIO_PuPd,GPIO_Speed_High_Default,GPIO_Mode
PC8.GPIO_Mode=GPIO_MODE_AF_PP
PC8.GPIO_PuPd=GPIO_PULLUP
PC8.GPIO_Speed_High_Default=GPIO_SPEED_FREQ_MEDIUM
PC8.Mode=SD_4_bits_Wide_bus
PC8.Signal=SDMMC1_D0
PC9.GPIOParameters=GPIO_PuPd,GPIO_Speed_High_Default,GPIO_Mode
PC9.GPIO_Mode=GPIO_MODE_AF_PP
PC9.GPIO_PuPd=GPIO_PULLUP
PC9.GPIO_Speed_High_Default=GPIO_SPEED_FREQ_MEDIUM
PC9.Mode=SD_4_bits_Wide_bus
PC9.Signal=SDMMC1_D1
PD0.Signal=FMC_D2_DA2
PD1.Signal=FMC_D3_DA3
PD10.Signal=FMC_D15_DA15
PD14.Signal=FMC_D0_DA0
PD15.Signal=FMC_D1_DA1
PD2.GPIOParameters=GPIO_PuPd,GPIO_Speed_High_Default,GPIO_Mode
PD2.GPIO_Mode=GPIO_MODE_AF_PP
PD2.GPIO_PuPd=GPIO_PULLUP
PD2.GPIO_Speed_High_Default=GPIO_SPEED_FREQ_MEDIUM
PD2.Mode=SD_4_bits_Wide_bus
PD2.Signal=SDMMC1_CMD
PD8.Signal=FMC_D13_DA13
PD9.Signal=FMC_D14_DA14
PE0.Signal=FMC_NBL0
PE1.Signal=FMC_NBL1
PE10.Signal=FMC_D7_DA7
PE11.Signal=FMC_D8_DA8
PE12.Signal=FMC_D9_DA9
PE13.Signal=FMC_D10_DA10
PE14.Signal=FMC_D11_DA11
PE15.Signal=FMC_D12_DA12
PE2.GPIOParameters=GPIO_Speed,GPIO_PuPd,GPIO_Mode
PE2.GPIO_Mode=GPIO_MODE_AF_PP
PE2.GPIO_PuPd=GPIO_NOPULL
PE2.GPIO_Speed=GPIO_SPEED_FREQ_VERY_HIGH
PE2.Mode=SAI_A_MasterWithClock
PE2.Signal=SAI1_MCLK_A
PE3.GPIOParameters=GPIO_Speed,GPIO_PuPd,GPIO_Mode
PE3.GPIO_Mode=GPIO_MODE_AF_PP
PE3.GPIO_PuPd=GPIO_NOPULL
PE3.GPIO_Speed=GPIO_SPEED_FREQ_VERY_HIGH
PE3.Mode=SAI_B_SyncSlave
PE3.Signal=SAI1_SD_B
PE4.GPIOParameters=GPIO_Speed,GPIO_PuPd,GPIO_Mode
PE4.GPIO_Mode=GPIO_MODE_AF_PP
PE4.GPIO_PuPd=GPIO_NOPULL
PE4.GPIO_Speed=GPIO_SPEED_FREQ_VERY_HIGH
PE4.Mode=SAI_A_MasterWithClock
PE4.Signal=SAI1_FS_A
PE5.GPIOParameters=GPIO_Speed,GPIO_PuPd,GPIO_Mode
PE5.GPIO_Mode=GPIO_MODE_AF_PP
PE5.GPIO_PuPd=GPIO_NOPULL
PE5.GPIO_Speed=GPIO_SPEED_FREQ_VERY_HIGH
PE5.Mode=SAI_A_MasterWithClock
PE5.Signal=SAI1_SCK_A
PE6.GPIOParameters=GPIO_Speed,GPIO_PuPd,GPIO_Mode
PE6.GPIO_Mode=GPIO_MODE_AF_PP
PE6.GPIO_PuPd=GPIO_NOPULL
PE6.GPIO_Speed=GPIO_SPEED_FREQ_VERY_HIGH
PE6.Mode=SAI_A_MasterWithClock
PE6.Signal=SAI1_SD_A
PE7.Signal=FMC_D4_DA4
PE8.Signal=FMC_D5_DA5
PE9.Signal=FMC_D6_DA6
PF0.Signal=FMC_A0
PF1.Signal=FMC_A1
PF11.Signal=FMC_SDNRAS
PF12.Signal=FMC_A6
PF13.Signal=FMC_A7
PF14.Signal=FMC_A8
PF15.Signal=FMC_A9
PF2.Signal=FMC_A2
PF3.Signal=FMC_A3
PF4.Signal=FMC_A4
PF5.Signal=FMC_A5
PF6.GPIOParameters=GPIO_Speed
PF6.GPIO_Speed=GPIO_SPEED_FREQ_HIGH
PF6.Mode=NSS_Signal_Hard_Input
PF6.Signal=SPI5_NSS
PF7.GPIOParameters=GPIO_Speed
PF7.GPIO_Speed=GPIO_SPEED_FREQ_HIGH
PF7.Mode=Full_Duplex_Slave
PF7.Signal=SPI5_SCK
PF8.Mode=Full_Duplex_Slave
PF8.Signal=SPI5_MISO
PF9.GPIOParameters=GPIO_Speed
PF9.GPIO_Speed=GPIO_SPEED_FREQ_HIGH
PF9.Mode=Full_Duplex_Slave
PF9.Signal=SPI5_MOSI
PG0.Signal=FMC_A10
PG1.Signal=FMC_A11
PG15.Signal=FMC_SDNCAS
PG2.Signal=FMC_A12
PG4.Signal=FMC_A14_BA0
PG5.Signal=FMC_A15_BA1
PG8.Signal=FMC_SDCLK
PH0-OSC_IN\ (PH0).Mode=HSE-External-Oscillator
PH0-OSC_IN\ (PH0).Signal=RCC_OSC_IN
PH1-OSC_OUT\ (PH1).Mode=HSE-External-Oscillator
PH1-OSC_OUT\ (PH1).Signal=RCC_OSC_OUT
RCC.SYSCLKFreq_VALUE=480000000
RCC.SYSCLKSource=RCC_SYSCLKSOURCE_PLLCLK
board=custom

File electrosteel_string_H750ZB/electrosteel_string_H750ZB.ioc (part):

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Mcu.Name=STM32H750ZBTx
Mcu.Package=LQFP144
Mcu.UserName=STM32H750ZBTx
PA0.Mode=IN16-Single-Ended
PA0.Signal=ADC1_INP16
PA1.Mode=IN17-Single-Ended
PA1.Signal=ADC1_INP17
PA15\ (JTDI).Mode=NSS_Signal_Hard_Input
PA15\ (JTDI).Signal=SPI3_NSS
PA2.Signal=ADCx_INP14
PA3.Signal=ADCx_INP15
PA4.Signal=ADCx_INP18
PA5.Signal=ADCx_INP19
PA6.Signal=ADCx_INP3
PA7.Signal=ADCx_INP7
PB0.Signal=ADCx_INP9
PB1.Signal=ADCx_INP5
PB12.GPIOParameters=GPIO_Speed
PB12.GPIO_Speed=GPIO_SPEED_FREQ_HIGH
PB12.Mode=NSS_Signal_Hard_Input
PB12.Signal=SPI2_NSS
PB13.GPIOParameters=GPIO_Speed
PB13.GPIO_Speed=GPIO_SPEED_FREQ_HIGH
PB13.Mode=Full_Duplex_Slave
PB13.Signal=SPI2_SCK
PB14.GPIOParameters=GPIO_Speed
PB14.GPIO_Speed=GPIO_SPEED_FREQ_HIGH
PB14.Mode=Full_Duplex_Slave
PB14.Signal=SPI2_MISO
PB15.GPIOParameters=GPIO_Speed
PB15.GPIO_Speed=GPIO_SPEED_FREQ_HIGH
PB15.Mode=Full_Duplex_Slave
PB15.Signal=SPI2_MOSI
PC10.Mode=Full_Duplex_Slave
PC10.Signal=SPI3_SCK
PC11.Mode=Full_Duplex_Slave
PC11.Signal=SPI3_MISO
PC12.Mode=Full_Duplex_Slave
PC12.Signal=SPI3_MOSI
PC4.Signal=ADCx_INP4
PC5.Signal=ADCx_INP8
PD11.Signal=GPXTI11
PD7.GPIOParameters=GPIO_Speed
PD7.GPIO_Speed=GPIO_SPEED_FREQ_HIGH
PD7.Mode=Full_Duplex_Master
PD7.Signal=SPI1_MOSI
PF11.Signal=GPIO_Output
PG10.GPIOParameters=GPIO_Speed
PG10.GPIO_Speed=GPIO_SPEED_FREQ_HIGH
PG10.Mode=NSS_Signal_Hard_Output
PG10.Signal=SPI1_NSS
PG11.GPIOParameters=GPIO_Speed
PG11.GPIO_Speed=GPIO_SPEED_FREQ_HIGH
PG11.Mode=Full_Duplex_Master
PG11.Signal=SPI1_SCK
PG9.GPIOParameters=GPIO_Speed
PG9.GPIO_Speed=GPIO_SPEED_FREQ_HIGH
PG9.Mode=Full_Duplex_Master
PG9.Signal=SPI1_MISO
PH0-OSC_IN\ (PH0).Mode=HSE-External-Oscillator
PH0-OSC_IN\ (PH0).Signal=RCC_OSC_IN
PH1-OSC_OUT\ (PH1).Mode=HSE-External-Oscillator
PH1-OSC_OUT\ (PH1).Signal=RCC_OSC_OUT
RCC.SYSCLKFreq_VALUE=480000000
RCC.SYSCLKSource=RCC_SYSCLKSOURCE_PLLCLK
board=custom
